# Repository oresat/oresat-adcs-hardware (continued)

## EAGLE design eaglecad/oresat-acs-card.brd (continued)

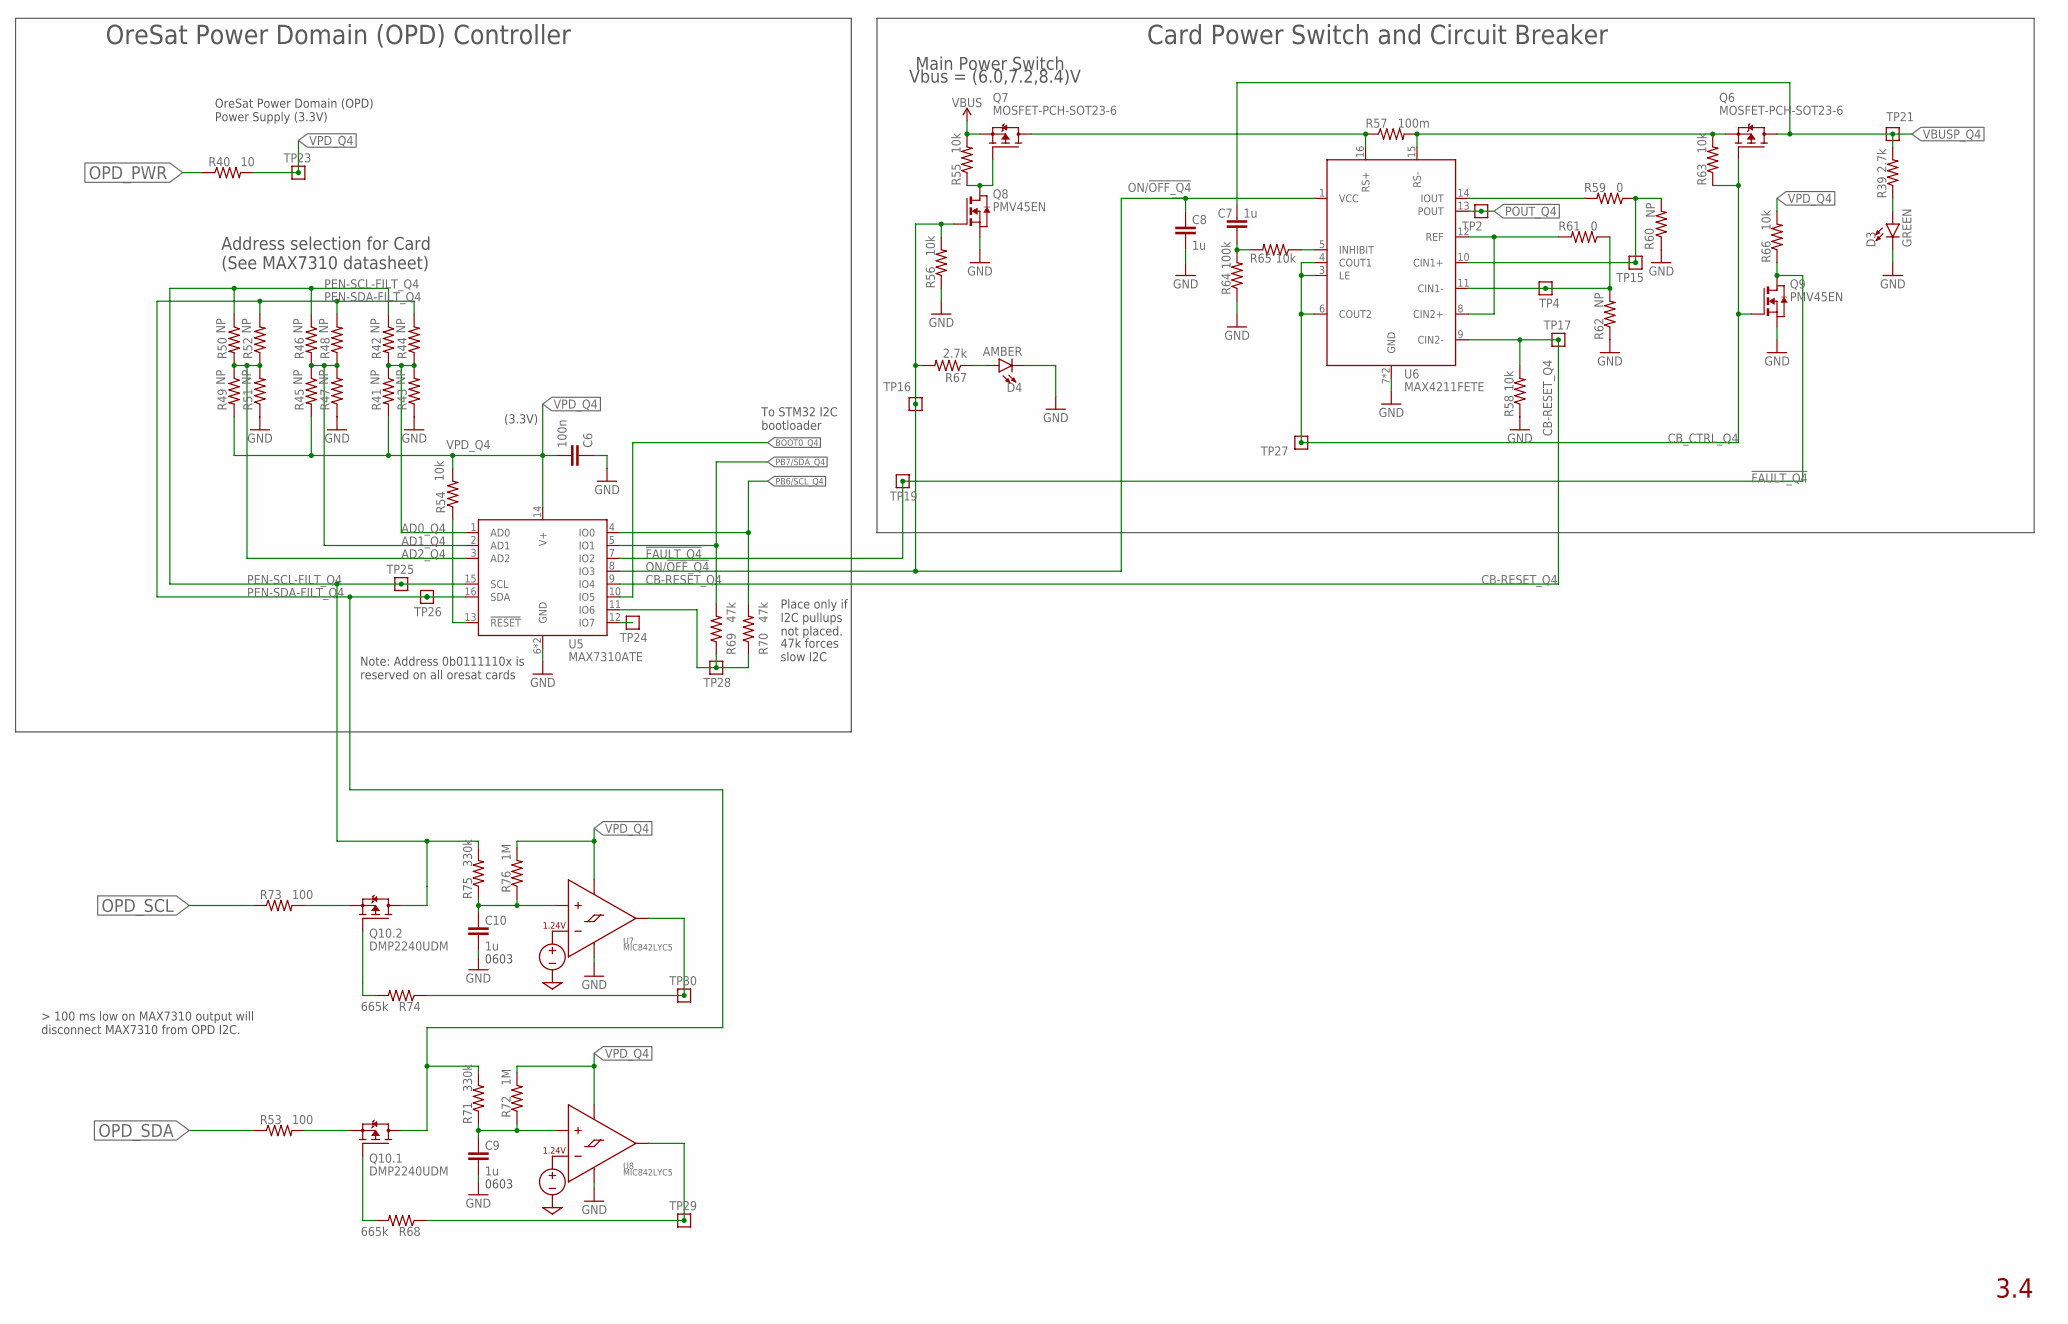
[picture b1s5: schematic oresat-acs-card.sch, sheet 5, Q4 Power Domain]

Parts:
C6: 100n; .0603-C-NOSILK; MPN CL10B104KB8NNNL
C7: 1u; .0603-C-NOSILK
C8, C9, C10: 1u; .0603-C-NOSILK; MPN CC0603KRX7R7BB105
D3: GREEN; LED-0603; MPN SML-E12M8WT86
D4: AMBER; LED-0603; MPN IN-S63AT5A
Q6, Q7: MOSFET-PCH-SOT23-6; SOT23-6; MPN DMP3050LVT-7
Q8, Q9: PMV45EN; SOT23; MPN PMV45EN2R
Q10: DMP2240UDM; SOT23-6; MPN DMP2240UDM
R39, R67: 2.7k; .0603-C-NOSILK; MPN CRGCQ0603F2K7
R40: 10; .0603-C-NOSILK; MPN RC0603FR-0710RL
R41, R42, R43, R44, R45, R46, R47, R48, R49, R50, R51, R52, R60, R62: NP; .0603-C-NOSILK; MPN RC1005F6653CS
R53, R73: 100; .0603-C-NOSILK; MPN RC0603FR-07100RL
R54, R55, R56, R58, R63, R66: 10k; .0603-C-NOSILK; MPN RC0603FR-0710KL
R57: 100m; R1206; MPN CSR1206FTR100
R59, R61: 0; .0603-C-NOSILK; MPN RC0603JR-070RL
R64: 100k; .0603-C-NOSILK; MPN RC1005F6653CS
R65: 10k; .0603-C-NOSILK; MPN RC1005F6653CS
R68, R74: 665k; .0603-C-NOSILK; MPN RC0603FR-07665KL
R69, R70: 47k; .0603-C-NOSILK; MPN RC0603FR-0747KL
R71, R75: 330k; .0603-C-NOSILK; MPN MCT06030C3303FP000
R72, R76: 1M; .0603-C-NOSILK; MPN RC0603FR-071ML
TP2, TP4, TP15, TP16, TP17, TP19, TP21, TP23, TP24, TP25, TP26, TP27, TP28, TP29, TP30: TEST-POINT-LARGE-SQUARE; 1X01
U5: MAX7310ATE; QFN65P400X400X80-17T210; MPN MAX7310ATE
U6: MAX4211FETE; QFN65P400X400X80-17T210; MPN MAX4211FETE
U7, U8: MIC842LYC5; SC70-5; MPN MIC842LYC5-TR

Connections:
!FAULT_Q4: Q9.3 (D), R66.1, TP19.1, U5.7 (IO2)
AD0_Q4: R41.1, R42.2, R43.2, R44.1, U5.1 (AD0)
AD1_Q4: R45.1, R46.2, R47.2, R48.1, U5.2 (AD1)
AD2_Q4: R49.1, R50.2, R51.2, R52.1, U5.3 (AD2)
BOOT0_Q4: U5.10 (IO5); also elsewhere on the board
CB-RESET_Q4: R58.2, TP17.1, U5.9 (IO4), U6.9 (CIN2-)
CB_CTRL_Q4: Q6.3 (G), Q9.1 (G), R63.1, TP27.1, U6.3 (LE), U6.4 (COUT1), U6.6 (COUT2)
GND: C6.1, C8.2, C9.2, C10.2, D3.C, D4.C, Q8.2 (S), Q9.2 (S), R43.1, R47.1, R51.1, R56.1, R58.1, R60.1, R62.1, R64.1, U5.6 (GND), U5.EPAD (GND), U6.7 (GND), U6.EPAD (GND), U7.2 (GND), U8.2 (GND); also elsewhere on the board
IOUT_Q4: R59.2, U6.14 (IOUT)
unnamed: D3.A, R39.1
unnamed: R54.1, U5.13 (!RESET)
unnamed: Q7.3 (G), Q8.3 (D), R55.1
unnamed: Q7.1 (D), Q7.2 (D), Q7.5 (D), Q7.6 (D), R57.1, U6.16 (RS+)
unnamed: R59.1, R60.2, TP15.1, U6.10 (CIN1+)
unnamed: R61.1, R62.2, TP4.1, U6.11 (CIN1-)
unnamed: R61.2, U6.8 (CIN2+), U6.12 (REF)
unnamed: R65.1, U6.5 (INHIBIT)
unnamed: C7.1, R64.2, R65.2
unnamed: Q6.4 (S), R57.2, R63.2, U6.15 (RS-)
unnamed: D4.A, R67.1
unnamed: Q10.5 (S), R53.2
unnamed: R68.1, TP29.1, U8.4 (OUT)
unnamed: R69.1, R70.1, TP28.1, U5.11 (IO6)
unnamed: Q10.2 (S), R73.2
unnamed: R74.1, TP30.1, U7.4 (OUT)
unnamed: C10.1, R75.1, R76.1, U7.1 (INP)
unnamed: C9.1, R71.1, R72.1, U8.1 (INP)
unnamed: TP24.1, U5.12 (IO7)
unnamed: Q10.3 (G), R74.2
unnamed: Q10.1 (G), R68.2
ON/!OFF_Q4: C8.1, Q8.1 (G), R56.2, R67.2, TP16.1, U5.8 (IO3), U6.1 (VCC)
OPD_PWR: R40.1; also elsewhere on the board
OPD_SCL: R73.1; also elsewhere on the board
OPD_SDA: R53.1; also elsewhere on the board
PB6/SCL_Q4: R70.2, U5.4 (IO0); also elsewhere on the board
PB7/SDA_Q4: R69.2, U5.5 (IO1); also elsewhere on the board
PEN-SCL-FILT_Q4: Q10.4 (D), R42.1, R46.1, R50.1, R75.2, TP25.1, U5.15 (SCL)
PEN-SDA-FILT_Q4: Q10.6 (D), R44.2, R48.2, R52.2, R71.2, TP26.1, U5.16 (SDA)
POUT_Q4: TP2.1, U6.13 (POUT)
VBUS: Q7.4 (S), R55.2; also elsewhere on the board
VBUSP_Q4: C7.2, Q6.1 (D), Q6.2 (D), Q6.5 (D), Q6.6 (D), R39.2, TP21.1; also elsewhere on the board
VPD_Q4: C6.2, R40.2, R41.2, R45.2, R49.2, R54.2, R66.2, R72.2, R76.2, TP23.1, U5.14 (V+), U7.5 (VDD), U8.5 (VDD)

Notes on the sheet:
Main Power Switch
Address selection for Card (See MAX7310 datasheet)
(3.3V)
Vbus = (6.0,7.2,8.4)V
OreSat Power Domain (OPD) Power Supply (3.3V)
OreSat Power Domain (OPD) Controller
Card Power Switch and Circuit Breaker
3.4
Note: Address 0b0111110x is reserved on all oresat cards
Place only if I2C pullups not placed.
47k forces slow I2C
0603
To STM32 I2C bootloader

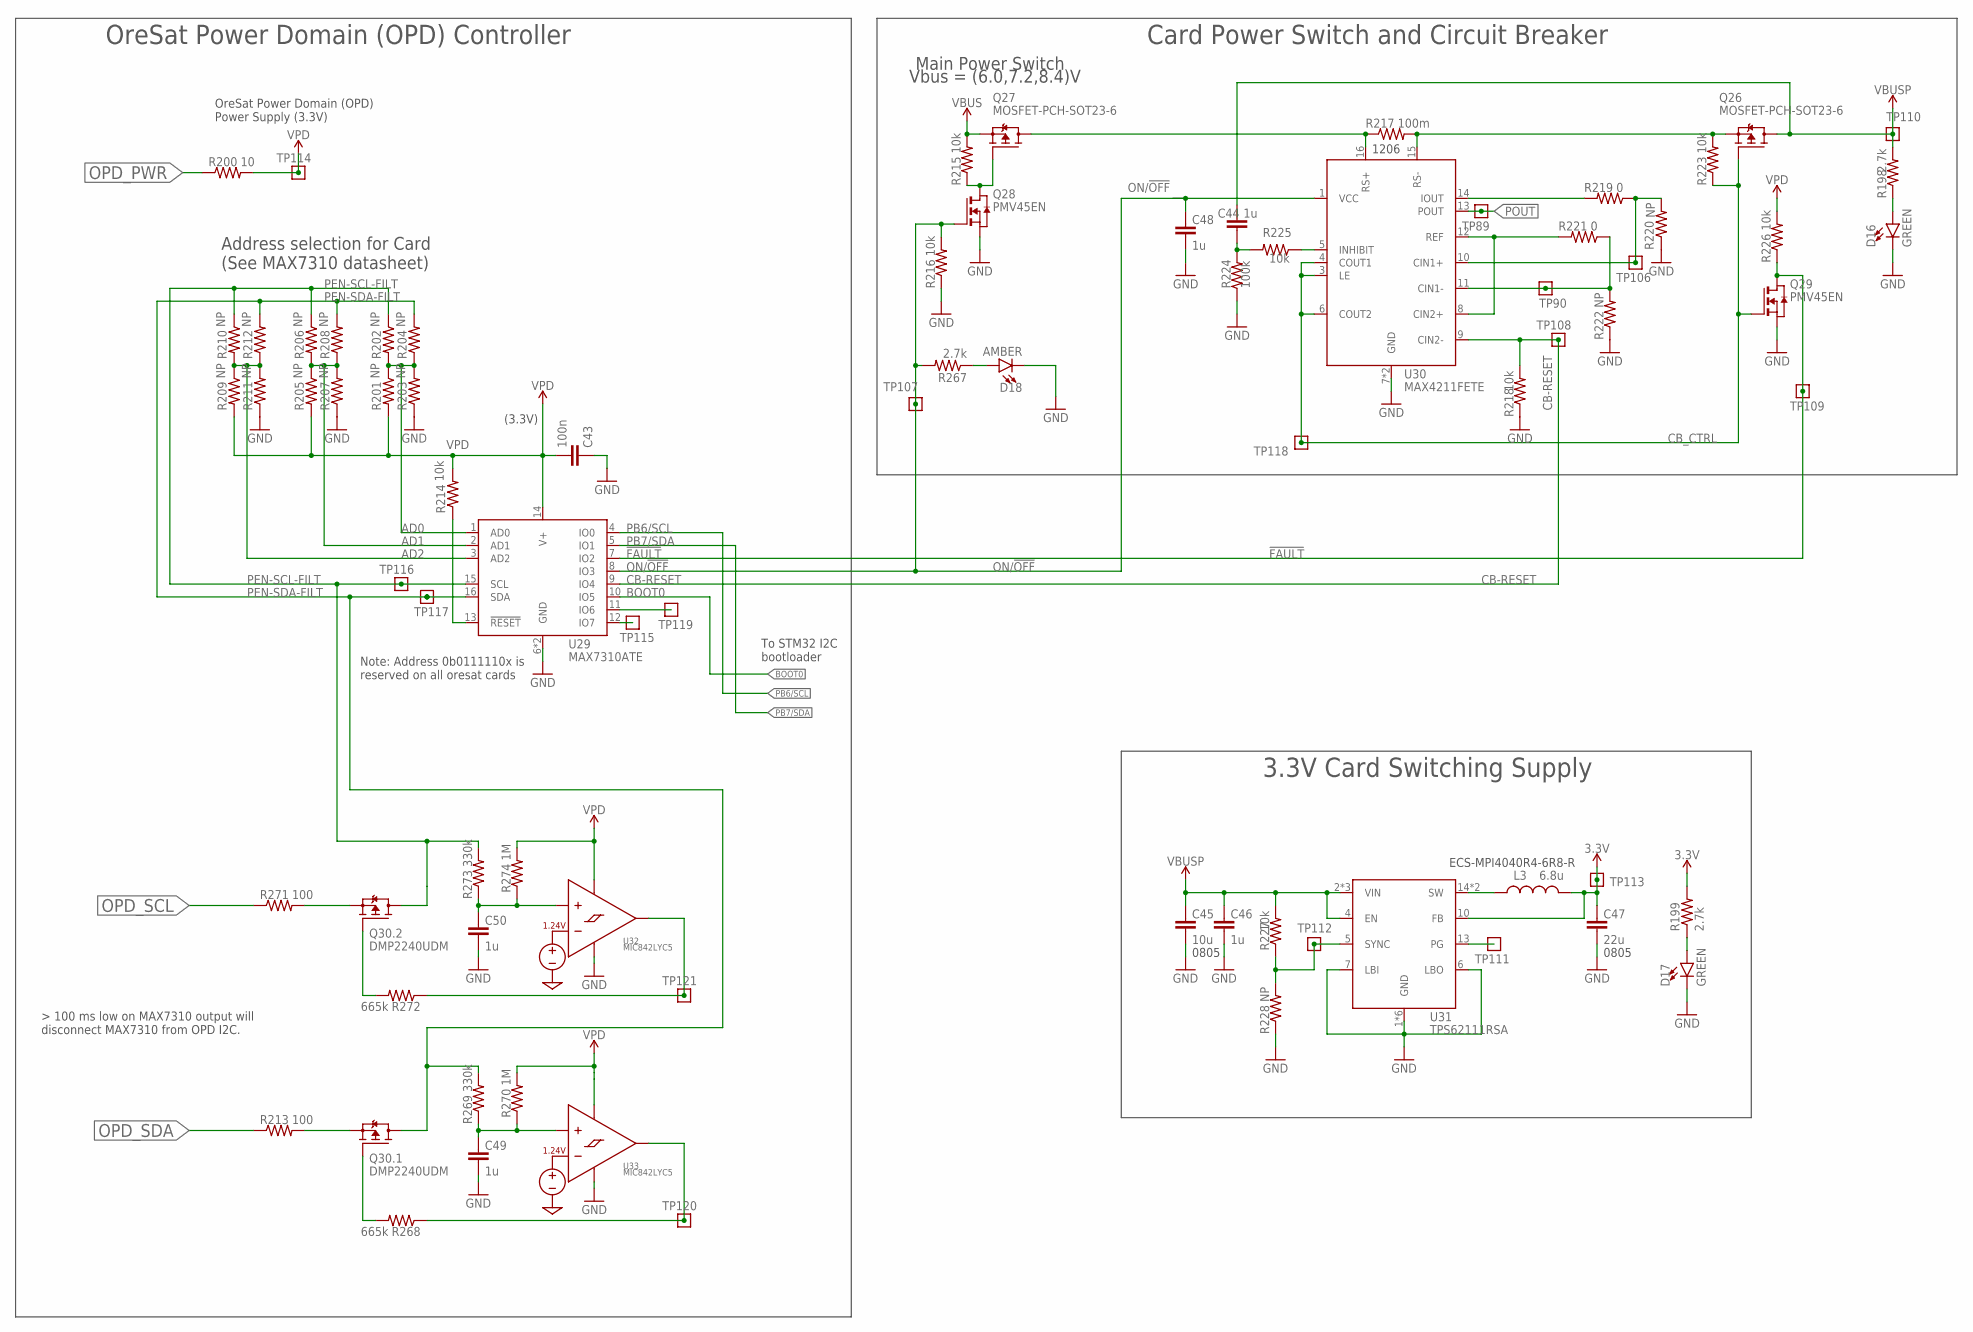
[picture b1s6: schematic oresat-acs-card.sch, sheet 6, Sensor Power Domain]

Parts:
C43: 100n; .0603-C-NOSILK; MPN CL10B104KB8NNNL
C44: 1u; .0603-C-NOSILK
C45: 10u; .0805-B-NOSILK; MPN CL21B106KOQNNNG
C46, C48, C49, C50: 1u; .0603-C-NOSILK; MPN CC0603KRX7R7BB105
C47: 22u; .0805-B-NOSILK; MPN GRM21BD71A226ME44L
D16, D17: GREEN; LED-0603; MPN SML-E12M8WT86
D18: AMBER; LED-0603; MPN IN-S63AT5A
L3: 6.8u; ECS-MPI4040; MPN ECS-MPI4040R4-6R8-R
Q26, Q27: MOSFET-PCH-SOT23-6; SOT23-6; MPN DMP3050LVT-7
Q28, Q29: PMV45EN; SOT23; MPN PMV45EN2R
Q30: DMP2240UDM; SOT23-6; MPN DMP2240UDM
R198, R199, R267: 2.7k; .0603-C-NOSILK; MPN CRGCQ0603F2K7
R200: 10; .0603-C-NOSILK; MPN RC0603FR-0710RL
R201, R202, R203, R204, R205, R206, R207, R208, R209, R210, R211, R212, R220, R222, R228: NP; .0603-C-NOSILK; MPN RC1005F6653CS
R213, R271: 100; .0603-C-NOSILK; MPN RC0603FR-07100RL
R214, R215, R216, R218, R223, R226, R227: 10k; .0603-C-NOSILK; MPN RC0603FR-0710KL
R217: 100m; R1206; MPN CSR1206FTR100
R219, R221: 0; .0603-C-NOSILK; MPN RC0603JR-070RL
R224: 100k; .0603-C-NOSILK; MPN RC1005F6653CS
R225: 10k; .0603-C-NOSILK; MPN RC1005F6653CS
R268, R272: 665k; .0603-C-NOSILK; MPN RC0603FR-07665KL
R269, R273: 330k; .0603-C-NOSILK; MPN MCT06030C3303FP000
R270, R274: 1M; .0603-C-NOSILK; MPN RC0603FR-071ML
TP89, TP90, TP106, TP107, TP108, TP109, TP110, TP111, TP112, TP113, TP114, TP115, TP116, TP117, TP118, TP119, TP120, TP121: TEST-POINT-LARGE-SQUARE; 1X01
U29: MAX7310ATE; QFN65P400X400X80-17T210; MPN MAX7310ATE
U30: MAX4211FETE; QFN65P400X400X80-17T210; MPN MAX4211FETE
U31: TPS62111RSA; S-PVQFN-16; MPN TPS62111RSA
U32, U33: MIC842LYC5; SC70-5; MPN MIC842LYC5-TR

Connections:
3.3V: C47.1, L3.2, R199.2, TP113.1, U31.10 (FB); also elsewhere on the board
!FAULT: Q29.3 (D), R226.1, TP109.1, U29.7 (IO2)
AD0: R201.1, R202.2, R203.2, R204.1, U29.1 (AD0)
AD1: R205.1, R206.2, R207.2, R208.1, U29.2 (AD1)
AD2: R209.1, R210.2, R211.2, R212.1, U29.3 (AD2)
BOOT0: U29.10 (IO5); also elsewhere on the board
CB-RESET: R218.2, TP108.1, U29.9 (IO4), U30.9 (CIN2-)
CB_CTRL: Q26.3 (G), Q29.1 (G), R223.1, TP118.1, U30.3 (LE), U30.4 (COUT1), U30.6 (COUT2)
GND: C43.1, C45.2, C46.2, C47.2, C48.2, C49.2, C50.2, D16.C, D17.C, D18.C, Q28.2 (S), Q29.2 (S), R203.1, R207.1, R211.1, R216.1, R218.1, R220.1, R222.1, R224.1, R228.1, U29.6 (GND), U29.EPAD (GND), U30.7 (GND), U30.EPAD (GND), U31.1 (GND), U31.6 (LBO), U31.7 (LBI), U31.9 (GND), U31.11 (GND), U31.12 (GND), U31.16 (GND), U31.PAD (GND), U32.2 (GND), U33.2 (GND); also elsewhere on the board
IOUT2: R219.2, U30.14 (IOUT)
unnamed: Q30.3 (G), R272.2
unnamed: Q30.1 (G), R268.2
unnamed: D16.A, R198.1
unnamed: D17.A, R199.1
unnamed: R214.1, U29.13 (!RESET)
unnamed: Q27.3 (G), Q28.3 (D), R215.1
unnamed: Q27.1 (D), Q27.2 (D), Q27.5 (D), Q27.6 (D), R217.1, U30.16 (RS+)
unnamed: R219.1, R220.2, TP106.1, U30.10 (CIN1+)
unnamed: R221.1, R222.2, TP90.1, U30.11 (CIN1-)
unnamed: R221.2, U30.8 (CIN2+), U30.12 (REF)
unnamed: R225.1, U30.5 (INHIBIT)
unnamed: C44.1, R224.2, R225.2
unnamed: Q26.4 (S), R217.2, R223.2, U30.15 (RS-)
unnamed: D18.A, R267.1
unnamed: Q30.5 (S), R213.2
unnamed: R268.1, TP120.1, U33.4 (OUT)
unnamed: TP119.1, U29.11 (IO6)
unnamed: Q30.2 (S), R271.2
unnamed: R272.1, TP121.1, U32.4 (OUT)
unnamed: C50.1, R273.1, R274.1, U32.1 (INP)
unnamed: C49.1, R269.1, R270.1, U33.1 (INP)
unnamed: TP115.1, U29.12 (IO7)
ON/!OFF: C48.1, Q28.1 (G), R216.2, R267.2, TP107.1, U29.8 (IO3), U30.1 (VCC)
OPD_PWR: R200.1; also elsewhere on the board
OPD_SCL: R271.1; also elsewhere on the board
OPD_SDA: R213.1; also elsewhere on the board
PB6/SCL: U29.4 (IO0); also elsewhere on the board
PB7/SDA: U29.5 (IO1); also elsewhere on the board
PEN-SCL-FILT: Q30.4 (D), R202.1, R206.1, R210.1, R273.2, TP116.1, U29.15 (SCL)
PEN-SDA-FILT: Q30.6 (D), R204.2, R208.2, R212.2, R269.2, TP117.1, U29.16 (SDA)
POUT: TP89.1, U30.13 (POUT); also elsewhere on the board
TPS62111-PG2: TP111.1, U31.13 (PG)
TPS62111-SYNC2: R227.1, R228.2, TP112.1, U31.5 (SYNC)
TPS62111_SW2: L3.1, U31.14 (SW), U31.15 (SW)
VBUS: Q27.4 (S), R215.2; also elsewhere on the board
VBUSP: C44.2, C45.1, C46.1, Q26.1 (D), Q26.2 (D), Q26.5 (D), Q26.6 (D), R198.2, R227.2, TP110.1, U31.2 (VIN), U31.3 (VIN), U31.4 (EN), U31.8 (VIN); also elsewhere on the board
VPD: C43.2, R200.2, R201.2, R205.2, R209.2, R214.2, R226.2, R270.2, R274.2, TP114.1, U29.14 (V+), U32.5 (VDD), U33.5 (VDD)

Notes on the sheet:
Main Power Switch
Address selection for Card (See MAX7310 datasheet)
(3.3V)
0805
ECS-MPI4040R4-6R8-R
Vbus = (6.0,7.2,8.4)V
OreSat Power Domain (OPD) Power Supply (3.3V)
OreSat Power Domain (OPD) Controller
3.3V Card Switching Supply
Card Power Switch and Circuit Breaker
Note: Address 0b0111110x is reserved on all oresat cards
To STM32 I2C bootloader
1206

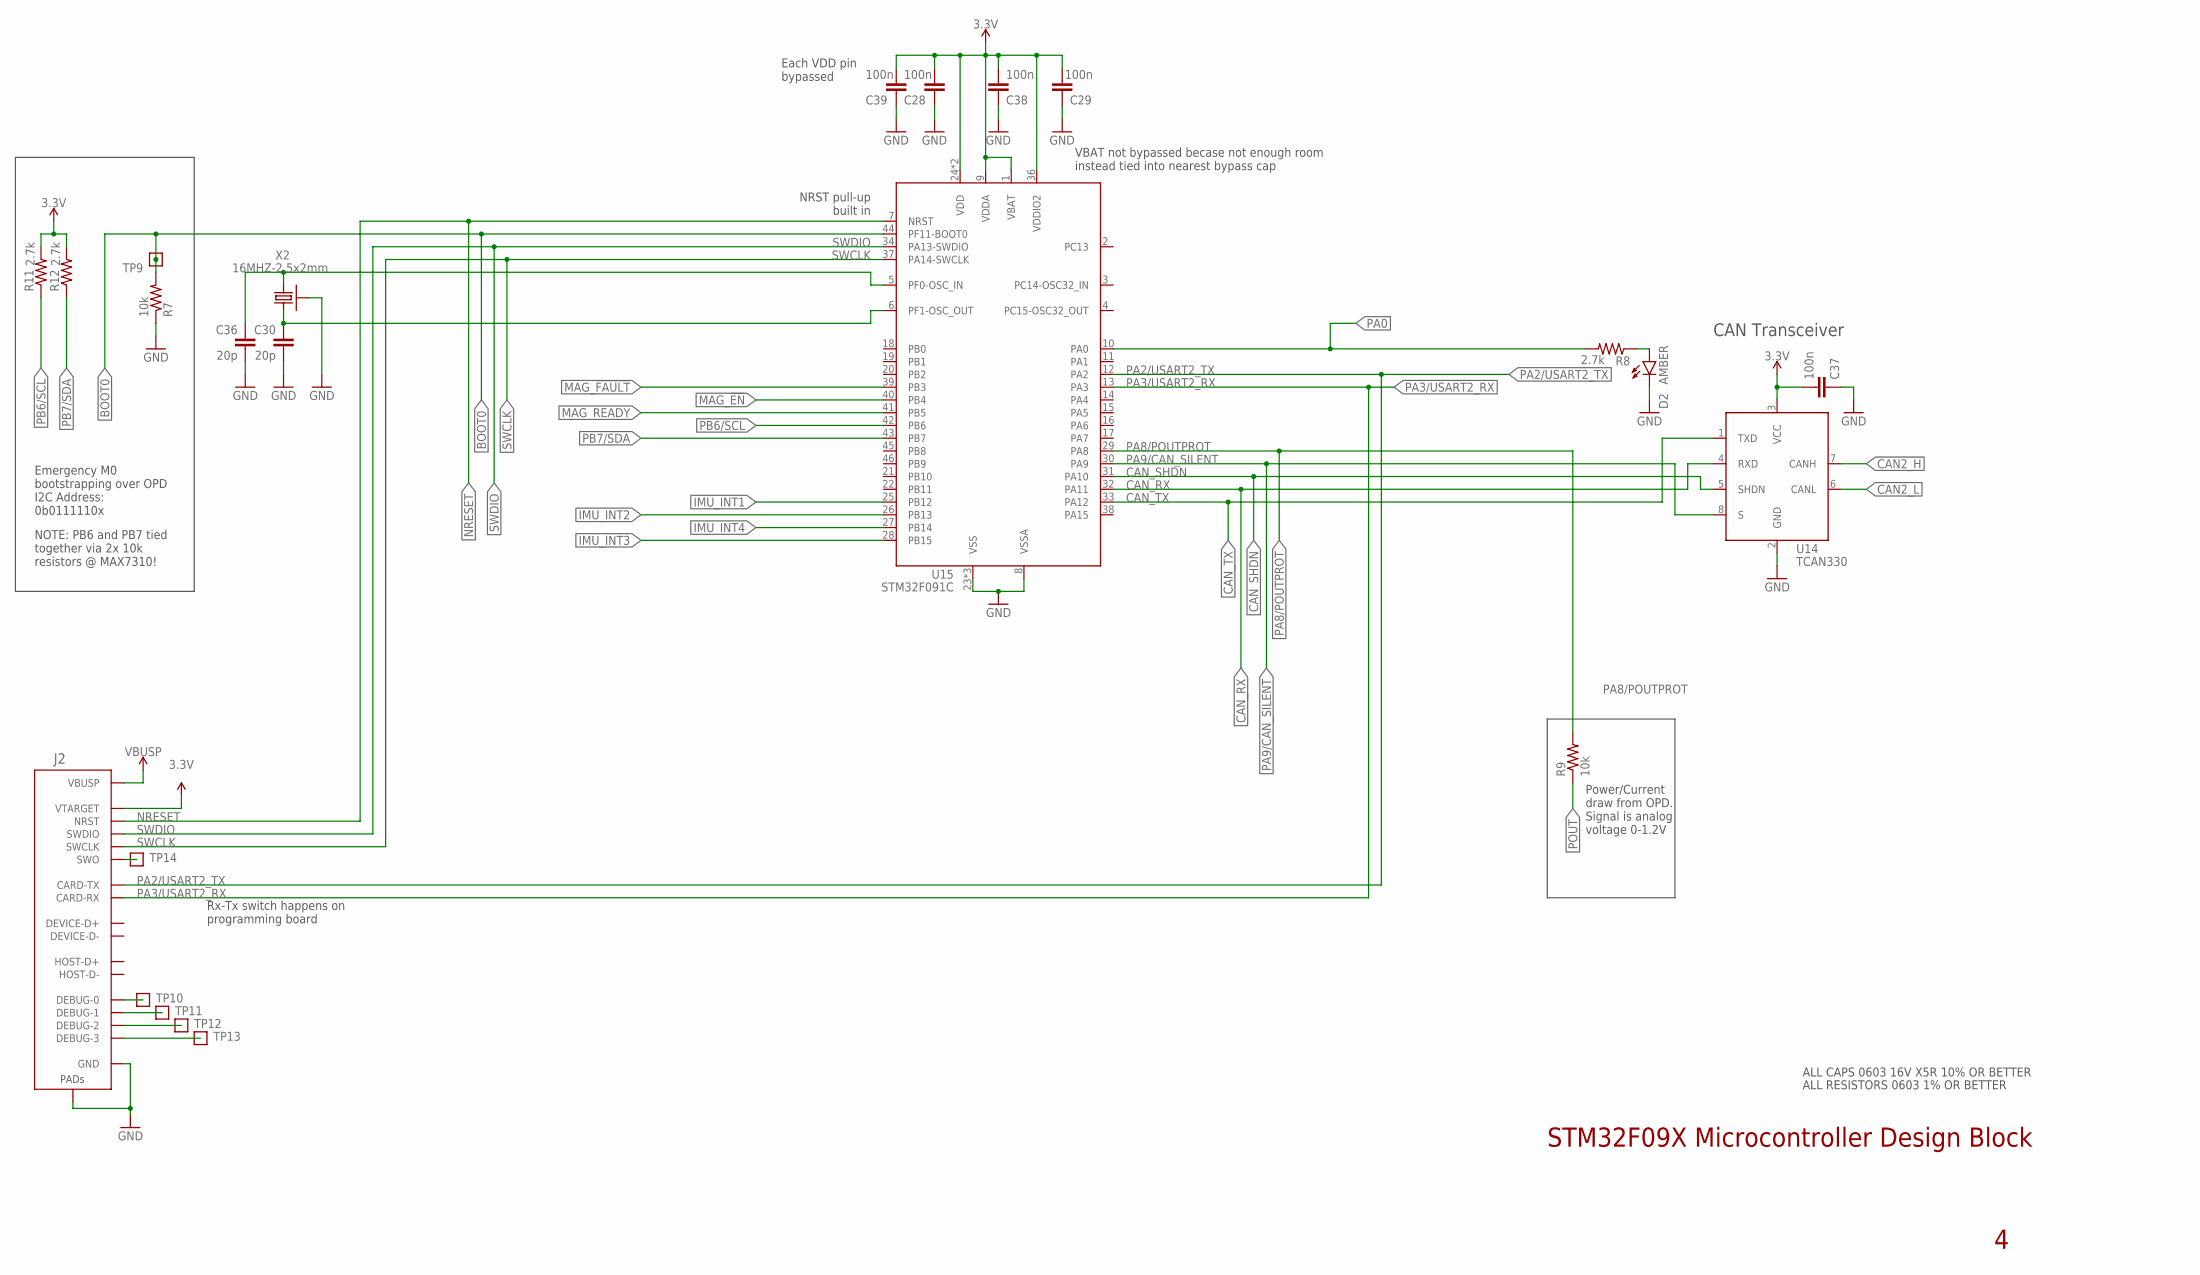
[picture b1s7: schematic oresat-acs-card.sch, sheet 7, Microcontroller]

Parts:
C28, C29, C37, C38, C39: 100n; .0603-C-NOSILK; MPN CL10B104KB8NNNL
C30, C36: 20p; .0603-C-NOSILK; MPN CL10C200JB8NNNC
D2: AMBER; LED-0603; MPN IN-S63AT5A
J2: ORESAT-DEBUG-CONNECTOR-SOLAR; WURTH_687120183622
R7, R9: 10k; .0603-C-NOSILK; MPN RC0603FR-0710KL
R8, R11, R12: 2.7k; .0603-C-NOSILK; MPN CRGCQ0603F2K7
TP9, TP10, TP11, TP12, TP13, TP14: TEST-POINT-LARGE-SQUARE; 1X01
U14: TCAN330; SOT23-8_TI-DCN; MPN TCAN330GDCNT
U15: STM32F091C; MPN STM32F042K6T7
X2: 16MHZ-2.5x2mm; CRYSTAL_2.5X2; MPN ECS-160-10-36Q-ES-TR

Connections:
3.3V: C28.2, C29.2, C37.2, C38.2, C39.2, J2.11 (VTARGET), R11.2, R12.2, U14.3 (VCC), U15.1 (VBAT), U15.9 (VDDA), U15.24 (VDD), U15.36 (VDDIO2), U15.48 (VDD); also elsewhere on the board
BOOT0: R7.2, TP9.1, U15.44 (PF11-BOOT0); also elsewhere on the board
CAN2_H: U14.7 (CANH); also elsewhere on the board
CAN2_L: U14.6 (CANL); also elsewhere on the board
CAN_RX: U14.4 (RXD), U15.32 (PA11)
CAN_SHDN: U14.5 (SHDN), U15.31 (PA10)
CAN_TX: U14.1 (TXD), U15.33 (PA12)
CRYSTALIN1: C36.1, U15.5 (PF0-OSC_IN), X2.1
CRYSTALOUT1: C30.1, U15.6 (PF1-OSC_OUT), X2.3 (2)
GND: C28.1, C29.1, C30.2, C36.2, C37.1, C38.1, C39.1, D2.C, J2.3 (GND), J2.6 (GND), J2.9 (GND), J2.PAD1 (PAD), J2.PAD2 (PAD), R7.1, U14.2 (GND), U15.8 (VSSA), U15.23 (VSS), U15.35 (VSS), U15.47 (VSS), X2.2 (SHIELD), X2.4 (SHIELD); also elsewhere on the board
IMU_INT1: U15.25 (PB12); also elsewhere on the board
IMU_INT2: U15.26 (PB13); also elsewhere on the board
IMU_INT3: U15.28 (PB15); also elsewhere on the board
IMU_INT4: U15.27 (PB14); also elsewhere on the board
MAG_!EN: U15.40 (PB4); also elsewhere on the board
MAG_!FAULT: U15.39 (PB3); also elsewhere on the board
MAG_READY: U15.41 (PB5); also elsewhere on the board
unnamed: D2.A, R8.1
unnamed: J2.20 (DEBUG-3), TP13.1
unnamed: J2.19 (DEBUG-2), TP12.1
unnamed: J2.18 (DEBUG-1), TP11.1
unnamed: J2.17 (DEBUG-0), TP10.1
unnamed: J2.16 (SWO), TP14.1
NRESET: J2.10 (NRST), U15.7 (NRST)
PA0: R8.2, U15.10 (PA0)
PA2/USART2_TX: J2.13 (CARD-TX), U15.12 (PA2)
PA3/USART2_RX: J2.12 (CARD-RX), U15.13 (PA3)
PA8/POUTPROT: R9.2, U15.29 (PA8)
PA9/CAN_SILENT: U14.8 (S), U15.30 (PA9)
PB6/SCL: R11.1, U15.42 (PB6); also elsewhere on the board
PB7/SDA: R12.1, U15.43 (PB7); also elsewhere on the board
POUT: R9.1; also elsewhere on the board
SWCLK: J2.15 (SWCLK), U15.37 (PA14-SWCLK)
SWDIO: J2.14 (SWDIO), U15.34 (PA13-SWDIO)
VBUSP: J2.1 (VBUSP), J2.2 (VBUSP); also elsewhere on the board

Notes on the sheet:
NRST pull-up built in
CAN Transceiver
Emergency M0 bootstrapping over OPD I2C Address: 0b0111110x
NOTE: PB6 and PB7 tied together via 2x 10k resistors @ MAX7310!
Power/Current draw from OPD. Signal is analog voltage 0-1.2V
Each VDD pin bypassed
VBAT not bypassed becase not enough room instead tied into nearest bypass cap
Rx-Tx switch happens on programming board
STM32F09X Microcontroller Design Block
ALL CAPS 0603 16V X5R 10% OR BETTER
ALL RESISTORS 0603 1% OR BETTER

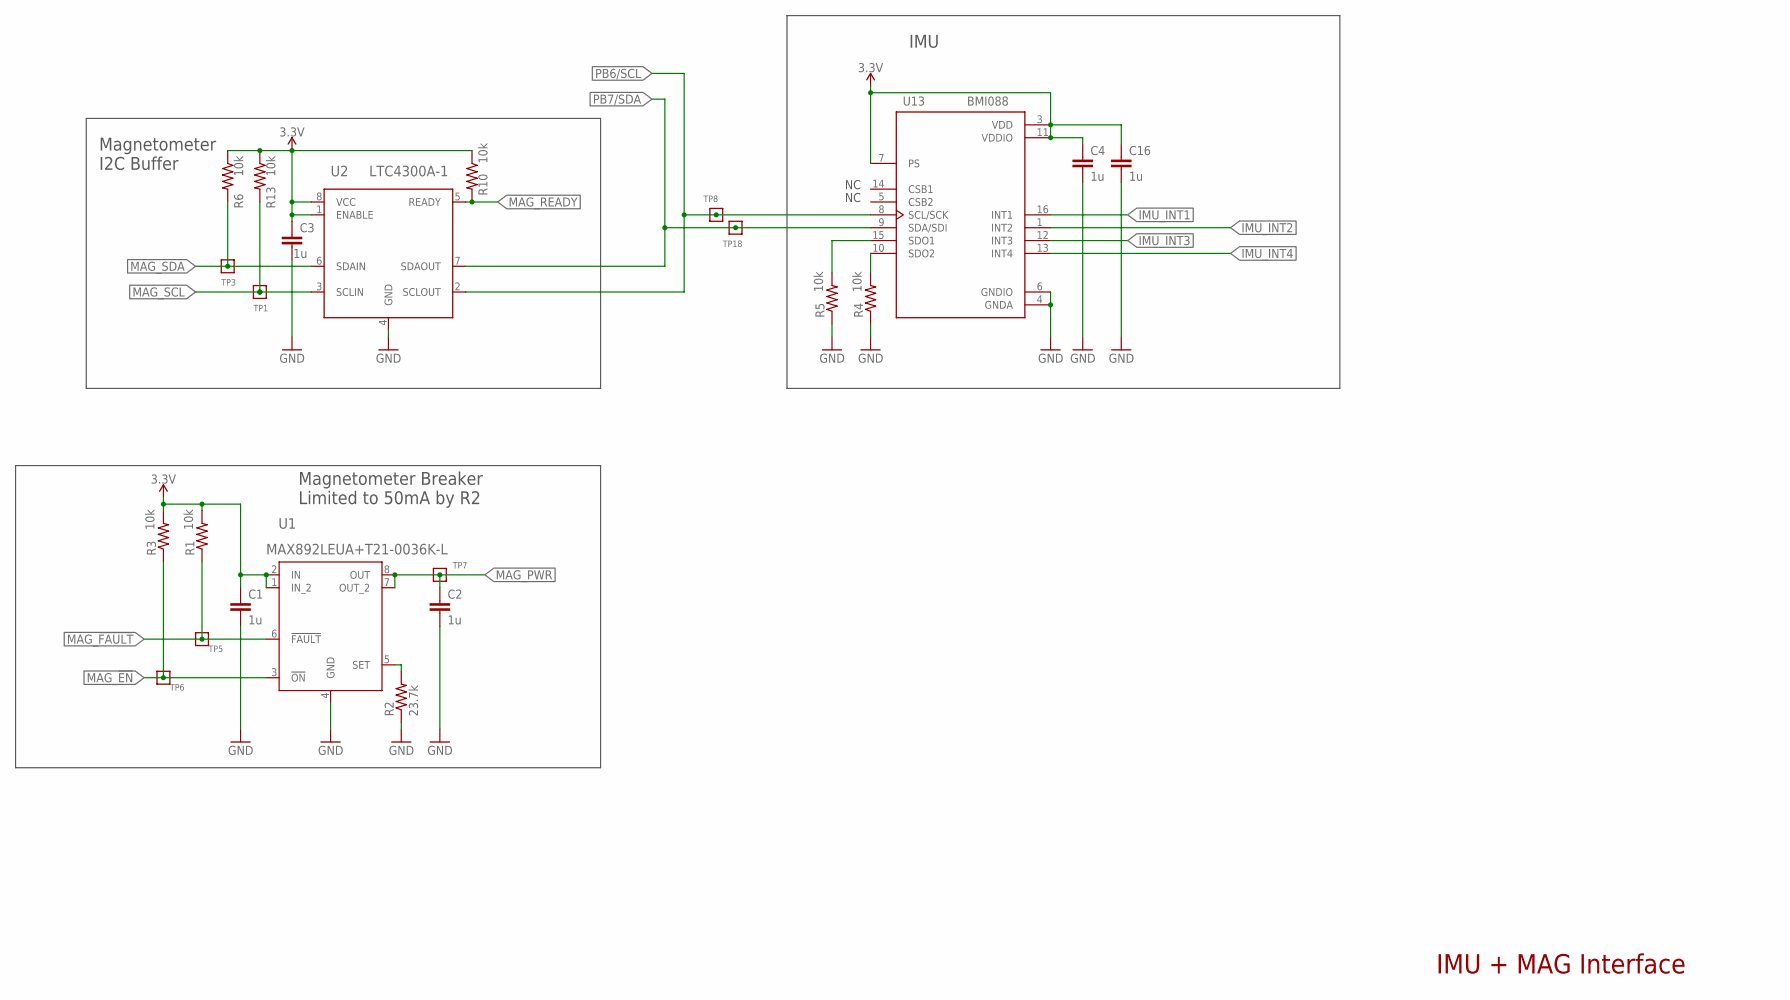
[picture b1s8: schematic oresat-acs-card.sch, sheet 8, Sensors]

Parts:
C1, C2, C3, C4, C16: 1u; .0603-C-NOSILK; MPN CC0603KRX7R7BB105
R1, R3, R4, R5, R6, R10, R13: 10k; .0603-C-NOSILK; MPN RC0603FR-0710KL
R2: 23.7k; .0603-C-NOSILK; MPN RC0603FR-0723K7L
TP1, TP3, TP5, TP6, TP7, TP8, TP18: TEST-POINT-LARGE-SQUARE; 1X01
U1: MAX892LEUA+T21-0036K-L; 21-0036K-L; MPN MAX892LEUA+
U2: LTC4300A-1; MS8; MPN LTC4300A-1IMS8#TRPBF
U13: BMI088; PQFN50P450X300X100-16N; MPN BMI088

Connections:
3.3V: C1.1, C3.1, C4.1, C16.1, R1.2, R3.2, R6.1, R10.1, R13.1, U1.1 (IN_2), U1.2 (IN), U2.1 (ENABLE), U2.8 (VCC), U13.3 (VDD), U13.7 (PS), U13.11 (VDDIO); also elsewhere on the board
GND: C1.2, C2.2, C3.2, C4.2, C16.2, R2.1, R4.1, R5.1, U1.4 (GND), U2.4 (GND), U13.4 (GNDA), U13.6 (GNDIO); also elsewhere on the board
IMU_INT1: U13.16 (INT1); also elsewhere on the board
IMU_INT2: U13.1 (INT2); also elsewhere on the board
IMU_INT3: U13.12 (INT3); also elsewhere on the board
IMU_INT4: U13.13 (INT4); also elsewhere on the board
MAG_!EN: R3.1, TP6.1, U1.3 (!ON); also elsewhere on the board
MAG_!FAULT: R1.1, TP5.1, U1.6 (!FAULT); also elsewhere on the board
MAG_PWR: C2.1, TP7.1, U1.7 (OUT_2), U1.8 (OUT); also elsewhere on the board
MAG_READY: R10.2, U2.5 (READY); also elsewhere on the board
MAG_SCL: R13.2, TP1.1, U2.3 (SCLIN); also elsewhere on the board
MAG_SDA: R6.2, TP3.1, U2.6 (SDAIN); also elsewhere on the board
unnamed: R4.2, U13.10 (SDO2)
unnamed: R5.2, U13.15 (SDO1)
unnamed: R2.2, U1.5 (SET)
PB6/SCL: TP8.1, U2.2 (SCLOUT), U13.8 (SCL/SCK); also elsewhere on the board
PB7/SDA: TP18.1, U2.7 (SDAOUT), U13.9 (SDA/SDI); also elsewhere on the board

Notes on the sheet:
Magnetometer I2C Buffer
Magnetometer Breaker Limited to 50mA by R2
IMU
IMU + MAG Interface
